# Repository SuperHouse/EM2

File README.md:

EtherMega2
==========
Copyright 2011-2018 Freetronics Pty Ltd www.freetronics.com.au  

The EtherMega2 is an Arduino-compatible board based on the existing
Arduino Mega2560, but with improvements and updates for features and
ease of use. It also includes on-board Ethernet with PoE (Power-over-
Ethernet) support.

Features:

 * High-efficiency switchmode power supply (input voltage 7-28Vdc)
 * Micro-USB Connector
 * microSD card slot
 * 10/100 Ethernet using the Wiznet W5500 chip
 * Overlay guide where you need it (both top and bottom)
 * D13 pin works for everything

You can learn more at:

  https://www.superhouse.tv/em2

INSTALLATION
------------
The design is saved as an EAGLE project. EAGLE PCB design software is
available from www.cadsoftusa.com free for non-commercial use. To use
this project download it and place the directory containing these files
into the "eagle" directory on your computer. Then open EAGLE and
navigate to the project.

DISTRIBUTION
------------
The specific terms of distribution of this project are governed by the
license referenced below.

LICENSE
-------
This work is licensed under the
Creative Commons Attribution-Share Alike License.  
To view a copy of this license, visit

  http://creativecommons.org/licenses/by-sa/3.0/  
  http://creativecommons.org/licenses/by-sa/3.0/legalcode

or send a letter to

  Creative Commons  
  171 Second Street, Suite 300  
  San Francisco  
  California, 94105  
  USA

The "license" folder within this repository also contains copies of the
licences referenced above.

CREDITS
-------
The EtherMega was designed by Jonathan Oxer (jon@freetronics.com) and
Marc Alexander (marc@freetronics.com) based on previous work by the Arduino
team (www.arduino.cc/playground/Main/People) which includes:

 * Massimo Banzi
 * David Cuartielles
 * Tom Igoe
 * Gianluca Martino
 * David A. Mellis

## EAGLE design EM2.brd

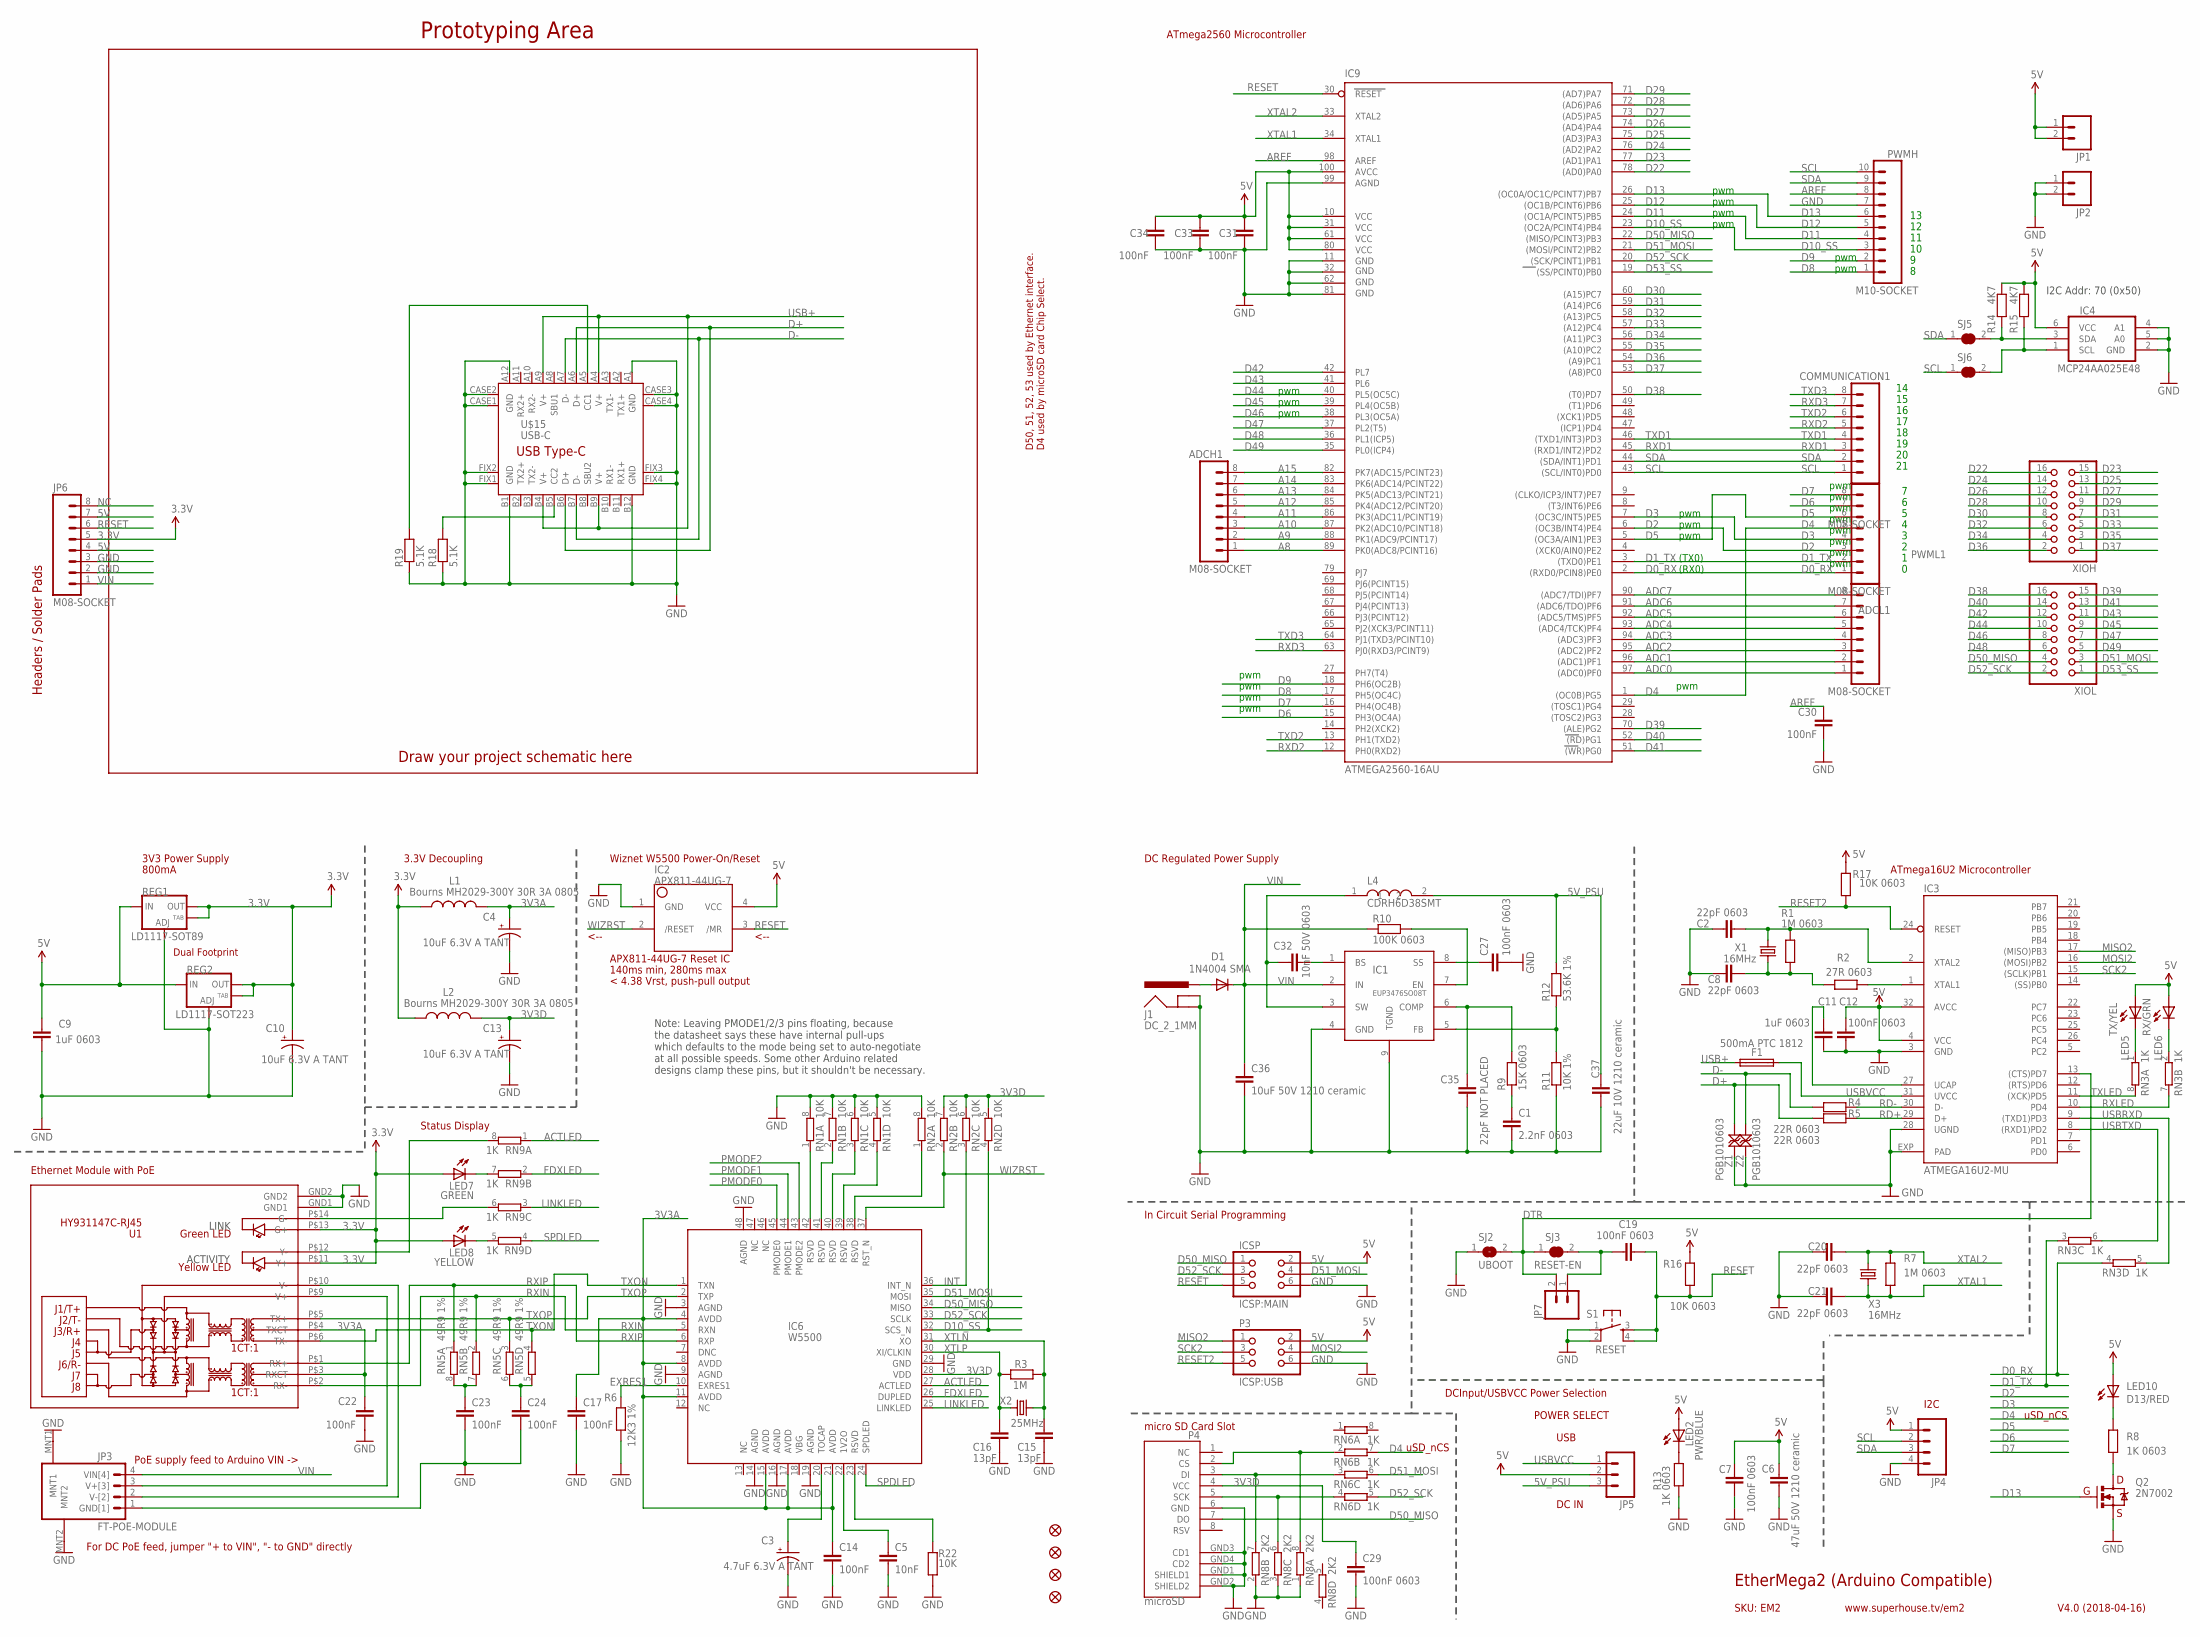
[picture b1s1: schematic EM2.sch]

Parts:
ADCH1: M08-SOCKET; 1X08-S
ADCL1: M08-SOCKET; 1X08-S
C1: 2.2nF 0603; C0603
C2, C8, C20, C21: 22pF 0603; C0603
C3: 4.7uF 6.3V A TANT; EIA3216
C4, C10, C13: 10uF 6.3V A TANT; EIA3216
C5: 10nF; C0603
C6: 47uF 50V 1210 ceramic; C1210
C7, C12, C19, C27, C29: 100nF 0603; C0603
C9, C11: 1uF 0603; C0603
C14, C17, C22, C23, C24, C30, C31, C33, C34: 100nF; C0603
C15, C16: 13pF; C0603
C32: 10nF 50V 0603; C0603
C35: 22pF NOT PLACED; C0603
C36: 10uF 50V 1210 ceramic; C1210
C37: 22uF 10V 1210 ceramic; C1210
COMMUNICATION1: M08-SOCKET; 1X08-S
D1: 1N4004 SMA; SMA-DIODE
F1: 500mA PTC 1812; 1812
FID1, FID2, FID3, FID4: FIDUCIAL1X2.5; FIDUCIAL-1X2.5
IC1: EUP3476SO08T; SO08T
IC2: APX811-44UG-7; SOT143-R
IC3: ATMEGA16U2-MU; ATMEL_QFN32
IC4: MCP24AA025E48; SOT23-6
IC6: W5500
IC9: ATMEGA2560-16AU; TQFP100
ICSP: ICSP:MAIN; 2X03-ICSP
J1: DC_2_1MM; POWER_JACK_SLOTS
JP1, JP2, JP7: M02PTH; 1X02
JP3: FT-POE-MODULE; FT-POE-MODULE-CLEAN
JP4: M04PTH; 1X04
JP5: M03-PIN; 1X03-P
JP6: M08-SOCKET; 1X08-S
L1, L2: Bourns MH2029-300Y 30R 3A 0805; L2012C
L4: CDRH6D38SMT; CDRH
LED2: PWR/BLUE; LED-0603
LED5: TX/YEL; LED-0603
LED6: RX/GRN; LED-0603
LED7: GREEN; LED-0603
LED8: YELLOW; LED-0603
LED10: D13/RED; LED-0603
P3: ICSP:USB; 2X03-ICSP
P4: microSD; MOLEX-SD-500901-003
PWMH: M10-SOCKET; 1X10-S
PWML1: M08-SOCKET; 1X08-S
Q2: 2N7002; SOT23-3
R1, R7: 1M 0603; R0603
R2: 27R 0603; R0603
R3: 1M; R0603
R4, R5: 22R 0603; R0603
R6: 12K3 1%; R0603
R8, R13: 1K 0603; R0603
R9: 15K 0603; R0603
R10: 100K 0603; R0603
R11: 10K 1%; R0603
R12: 53.6K 1%; R0603
R14, R15: 4K7; R0603
R16, R17: 10K 0603; R0603
R18, R19: 5.1K; R0603
R22: 10K; R0603
REG1: LD1117-SOT89; SOT89
REG2: LD1117-SOT223; SOT223
RN1, RN2: 10K; CAY16
RN3, RN6, RN9: 1K; CAY16
RN5: 49R9 1%; CAY16
RN8: 2K2; CAY16
S1: RESET; TACTILE_SMT-6MM
SJ2: UBOOT; SJ
SJ3: RESET-EN; SJC
SJ5, SJ6: SJCN; SJC
U1: HY931147C-RJ45; HY931147C
U$15: USB-C; USB-C-U52A
X1, X3: 16MHz; HC49U-V
X2: 25MHz; HC49U-V
XIOH: PINHD-2X8; 2X08
XIOL: PINHD-2X8; 2X08
Z1, Z2: PGB1010603; TVS0603

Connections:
3.3V: C10.A (+), JP6.5, L1.1, L2.1, LED7.A, LED8.A, REG1.2 (OUT), REG1.4 (OUT), REG2.2 (OUT), REG2.4 (OUT), U1.P$11 (Y+), U1.P$13 (G+)
3V3A: C4.A (+), C14.1, C17.1, C22.1, IC6.4 (AVDD), IC6.8 (AVDD), IC6.11 (AVDD), IC6.15 (AVDD), IC6.17 (AVDD), IC6.21 (AVDD), L1.2, U1.P$3 (RXCT), U1.P$4 (TXCT)
3V3D: C13.A (+), C29.1, IC6.28 (VDD), L2.2, P4.4 (VCC), RN2.5 (2), RN2.6 (2), RN2.7 (2)
5V: C6.2, C7.1, C9.1, C12.1, C31.1, C33.1, C34.1, IC2.4 (VCC), IC3.4 (VCC), IC3.32 (AVCC), IC4.6 (VCC), IC9.10 (VCC), IC9.31 (VCC1), IC9.61 (VCC2), IC9.80 (VCC3), IC9.100 (AVCC), ICSP.2, JP1.1, JP1.2, JP4.1, JP5.2, JP6.4, JP6.7, LED2.A, LED5.A, LED6.A, LED10.A, P3.2, R14.1, R15.1, R16.2, R17.2, REG1.3 (IN), REG2.3 (IN)
5V_PSU: C37.1, JP5.3, L4.2, R12.2
A8: ADCH1.1, IC9.89 (PK0(ADC8/PCINT16))
A9: ADCH1.2, IC9.88 (PK1(ADC9/PCINT17))
A10: ADCH1.3, IC9.87 (PK2(ADC10/PCINT18))
A11: ADCH1.4, IC9.86 (PK3(ADC11/PCINT19))
A12: ADCH1.5, IC9.85 (PK4(ADC12/PCINT20))
A13: ADCH1.6, IC9.84 (PK5(ADC13/PCINT21))
A14: ADCH1.7, IC9.83 (PK6(ADC14/PCINT22))
A15: ADCH1.8, IC9.82 (PK7(ADC15/PCINT23))
ACTLED: IC6.27 (ACTLED), RN9.1
ADC0: ADCL1.1, IC9.97 ((ADC0)PF0)
ADC1: ADCL1.2, IC9.96 ((ADC1)PF1)
ADC2: ADCL1.3, IC9.95 ((ADC2)PF2)
ADC3: ADCL1.4, IC9.94 ((ADC3)PF3)
ADC4: ADCL1.5, IC9.93 ((ADC4/TCK)PF4)
ADC5: ADCL1.6, IC9.92 ((ADC5/TMS)PF5)
ADC6: ADCL1.7, IC9.91 ((ADC6/TDO)PF6)
ADC7: ADCL1.8, IC9.90 ((ADC7/TDI)PF7)
AREF: C30.1, IC9.98 (AREF), PWMH.8
D0_RX: IC9.2 ((RXD0/PCIN8)PE0), PWML1.1, RN3.4 (1)
D1_TX: IC9.3 ((TXD0)PE1), PWML1.2, RN3.3 (1)
D2: IC9.6 ((OC3B/INT4)PE4), PWML1.3
D3: IC9.7 ((OC3C/INT5)PE5), PWML1.4
D4: IC9.1 ((OC0B)PG5), PWML1.5, RN6.7 (2)
D5: IC9.5 ((OC3A/AIN1)PE3), PWML1.6
D6: IC9.15 (PH3(OC4A)), PWML1.7
D7: IC9.16 (PH4(OC4B)), PWML1.8
D8: IC9.17 (PH5(OC4C)), PWMH.1
D9: IC9.18 (PH6(OC2B)), PWMH.2
D10_SS: IC6.32 (SCS_N), IC9.23 ((OC2A/PCINT4)PB4), PWMH.3, RN2.4 (1)
D11: IC9.24 ((OC1A/PCINT5)PB5), PWMH.4
D12: IC9.25 ((OC1B/PCINT6)PB6), PWMH.5
D13: IC9.26 ((OC0A/OC1C/PCINT7)PB7), PWMH.6, Q2.1 (G)
D22: IC9.78 ((AD0)PA0), XIOH.16
D23: IC9.77 ((AD1)PA1), XIOH.15
D24: IC9.76 ((AD2)PA2), XIOH.14
D25: IC9.75 ((AD3)PA3), XIOH.13
D26: IC9.74 ((AD4)PA4), XIOH.12
D27: IC9.73 ((AD5)PA5), XIOH.11
D28: IC9.72 ((AD6)PA6), XIOH.10
D29: IC9.71 ((AD7)PA7), XIOH.9
D30: IC9.60 ((A15)PC7), XIOH.8
D31: IC9.59 ((A14)PC6), XIOH.7
D32: IC9.58 ((A13)PC5), XIOH.6
D33: IC9.57 ((A12)PC4), XIOH.5
D34: IC9.56 ((A11)PC3), XIOH.4
D35: IC9.55 ((A10)PC2), XIOH.3
D36: IC9.54 ((A9)PC1), XIOH.2
D37: IC9.53 ((A8)PC0), XIOH.1
D38: IC9.50 ((T0)PD7), XIOL.16
D39: IC9.70 ((ALE)PG2), XIOL.15
D40: IC9.52 ((RD)PG1), XIOL.14
D41: IC9.51 ((WR)PG0), XIOL.13
D42: IC9.42 (PL7), XIOL.12
D43: IC9.41 (PL6), XIOL.11
D44: IC9.40 (PL5(OC5C)), XIOL.10
D45: IC9.39 (PL4(OC5B)), XIOL.9
D46: IC9.38 (PL3(OC5A)), XIOL.8
D47: IC9.37 (PL2(T5)), XIOL.7
D48: IC9.36 (PL1(ICP5)), XIOL.6
D49: IC9.35 (PL0(ICP4)), XIOL.5
D50_MISO: IC6.34 (MISO), IC9.22 ((MISO/PCINT3)PB3), ICSP.1, P4.7 (DO), XIOL.4
D51_MOSI: IC6.35 (MOSI), IC9.21 ((MOSI/PCINT2)PB2), ICSP.4, RN6.6 (2), XIOL.3
D52_SCK: IC6.33 (SCLK), IC9.20 ((SCK/PCINT1)PB1), ICSP.3, RN6.5 (2), XIOL.2
D53_SS: IC9.19 ((SS/PCINT0)PB0), XIOL.1
D+: R5.2, U$15.A6 (D+), U$15.B6 (D+), Z1.1
D-: R4.2, U$15.A7 (D-), U$15.B7 (D-), Z2.1
DTR: IC3.13 ((CTS)PD7), JP7.2, SJ2.2, SJ3.1
EXRES1: IC6.10 (EXRES1), R6.2
FDXLED: IC6.26 (DUPLED), RN9.2 (1)
GND: C1.2, C2.1, C3.C (-), C4.C (-), C5.2, C6.1, C7.2, C8.1, C9.2, C10.C (-), C11.2, C12.2, C13.C (-), C14.2, C15.2, C16.2, C17.2, C20.1, C21.1, C22.2, C23.2, C24.2, C27.2, C29.2, C30.2, C31.2, C33.2, C34.2, C35.2, C36.2, C37.2, IC1.4 (GND), IC1.9 (TGND), IC2.1 (GND), IC3.3 (GND), IC3.28 (UGND), IC3.EXP (PAD), IC4.2 (GND), IC4.4 (A1), IC4.5 (A0), IC6.3 (AGND), IC6.9 (AGND), IC6.14 (AGND), IC6.16 (AGND), IC6.19 (AGND), IC6.29 (GND), IC6.48 (AGND), IC9.11 (GND), IC9.32 (GND1), IC9.62 (GND2), IC9.81 (GND3), IC9.99 (AGND), ICSP.6, J1.GND, J1.GNDBREAK, JP2.1, JP2.2, JP3.1 (GND[1]), JP3.MNT1, JP3.MNT2, JP4.4, JP6.2, JP6.3, P3.6, P4.6 (GND), P4.GND1 (SHIELD1), P4.GND2 (SHIELD2), P4.GND3 (CD1), P4.GND4 (CD2), PWMH.7, Q2.2 (S), R6.1, R11.1, R13.1, R18.1, R19.1, R22.1, REG1.1 (ADJ), REG2.1 (ADJ), RN1.5 (2), RN1.6 (2), RN1.7 (2), RN1.8 (2), RN2.8 (2), RN8.1, RN8.2 (1), RN8.3 (1), S1.1, S1.2, SJ2.1, U1.GND1, U1.GND2, U$15.A1 (GND), U$15.A12 (GND), U$15.B1 (GND), U$15.B12 (GND), U$15.CASE1 (GND), U$15.CASE2 (GND), U$15.CASE3 (GND), U$15.CASE4 (GND), U$15.FIX1 (GND), U$15.FIX2 (GND), U$15.FIX3 (GND), U$15.FIX4 (GND), Z1.2, Z2.2
INT: IC6.36 (INT_N), RN2.3 (1)
LINKLED: IC6.25 (LINKLED), RN9.3 (1)
MISO2: IC3.17 ((MISO)PB3), P3.1
MOSI2: IC3.16 ((MOSI)PB2), P3.4
unnamed: C24.1, RN5.5 (2), RN5.6 (2)
unnamed: LED10.C, R8.2
unnamed: Q2.3 (D), R8.1
unnamed: IC3.1 (XTAL1), R2.1
unnamed: IC4.1 (SCL), R15.2, SJ6.2
unnamed: LED6.C, RN3.2 (1)
unnamed: LED2.C, R13.2
unnamed: LED5.C, RN3.1
unnamed: R18.2, U$15.B5 (CC2)
unnamed: IC4.3 (SDA), R14.2, SJ5.2
unnamed: P4.5 (SCK), RN6.4 (1), RN8.6 (2)
unnamed: P4.2 (CS), RN6.2 (1), RN8.8 (2)
unnamed: P4.3 (DI), RN6.3 (1), RN8.7 (2)
unnamed: LED8.C, RN9.5 (2)
unnamed: RN9.6 (2), U1.P$14 (G-)
unnamed: D1.A, J1.PWR
unnamed: IC6.39 (RSVD), RN1.4 (1)
unnamed: IC6.40 (RSVD), RN1.3 (1)
unnamed: C27.1, IC1.8 (SS)
unnamed: C1.1, R9.1
unnamed: C35.1, IC1.6 (COMP), R9.2
unnamed: R19.2, U$15.A5 (CC1)
unnamed: JP3.3 (V+[3]), U1.P$9 (V+)
unnamed: JP3.2 (V-[2]), U1.P$10 (V-)
unnamed: C32.1, IC1.3 (SW), L4.1
unnamed: C32.2, IC1.1 (BS)
unnamed: IC1.7 (EN), R10.2
unnamed: IC6.41 (RSVD), RN1.2 (1)
unnamed: C19.1, JP7.1, SJ3.2
unnamed: IC6.42 (RSVD), RN1.1
unnamed: IC1.5 (FB), R11.2, R12.1
unnamed: IC6.23 (RSVD), R22.2
unnamed: IC6.38 (RSVD), RN2.1
unnamed: C5.1, IC6.22 (1V2O)
unnamed: C3.A (+), IC6.20 (TOCAP)
unnamed: C2.2, IC3.2 (XTAL2), R1.2, X1.2
unnamed: C8.2, R1.1, R2.2, X1.1
unnamed: C11.1, IC3.27 (UCAP)
unnamed: C23.1, RN5.7 (2), RN5.8 (2)
unnamed: LED7.C, RN9.7 (2)
unnamed: RN9.8 (2), U1.P$12 (Y-)
NC: JP6.8
PMODE0: IC6.45 (PMODE0)
PMODE1: IC6.44 (PMODE1)
PMODE2: IC6.43 (PMODE2)
RD+: IC3.29 (D+), R5.1
RD-: IC3.30 (D-), R4.1
RESET: C19.2, IC2.3 (/MR), IC9.30 (RESET), ICSP.5, JP6.6, R16.1, S1.3, S1.4
RESET2: IC3.24 (RESET), P3.5, R17.1
RXD1: COMMUNICATION1.3, IC9.45 ((RXD1/INT2)PD2)
RXD2: COMMUNICATION1.5, IC9.12 (PH0(RXD2))
RXD3: COMMUNICATION1.7, IC9.63 (PJ0(RXD3/PCINT9))
RXIN: IC6.5 (RXN), RN5.2 (1), U1.P$2 (RX-)
RXIP: IC6.6 (RXP), RN5.1, U1.P$1 (RX+)
RXLED: IC3.10 (PD4), RN3.7 (2)
SCK2: IC3.15 ((SCLK)PB1), P3.3
SCL: COMMUNICATION1.1, IC9.43 ((SCL/INT0)PD0), JP4.2, PWMH.10, SJ6.1
SDA: COMMUNICATION1.2, IC9.44 ((SDA/INT1)PD1), JP4.3, PWMH.9, SJ5.1
SPDLED: IC6.24 (SPDLED), RN9.4 (1)
TXD1: COMMUNICATION1.4, IC9.46 ((TXD1/INT3)PD3)
TXD2: COMMUNICATION1.6, IC9.13 (PH1(TXD2))
TXD3: COMMUNICATION1.8, IC9.64 (PJ1(TXD3/PCINT10))
TXLED: IC3.11 ((XCK)PD5), RN3.8 (2)
TXON: IC6.1 (TXN), RN5.4 (1), U1.P$6 (TX-)
TXOP: IC6.2 (TXP), RN5.3 (1), U1.P$5 (TX+)
USB+: F1.1, U$15.A4 (V+), U$15.A9 (V+), U$15.B4 (V+), U$15.B9 (V+)
USBRXD: IC3.9 ((TXD1)PD3), RN3.5 (2)
USBTXD: IC3.8 ((RXD1)PD2), RN3.6 (2)
USBVCC: F1.2, IC3.31 (UVCC), JP5.1
VIN: C36.1, D1.C, IC1.2 (IN), JP3.4 (VIN[4]), JP6.1, R10.1
WIZRST: IC2.2 (/RESET), IC6.37 (RST_N), RN2.2 (1)
XTAL1: C21.2, IC9.34 (XTAL1), R7.1, X3.1
XTAL2: C20.2, IC9.33 (XTAL2), R7.2, X3.2
XTLN: C15.1, IC6.31 (XO), R3.1, X2.1
XTLP: C16.1, IC6.30 (XI/CLKIN), R3.2, X2.2

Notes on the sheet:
Prototyping Area
3V3 Power Supply
Status Display
Headers / Solder Pads
Dual Footprint
3.3V Decoupling
Draw your project schematic here
D50, 51, 52, 53 used by Ethernet interface.
PoE supply feed to Arduino VIN ->
For DC PoE feed, jumper "+ to VIN", "- to GND" directly
DC Regulated Power Supply
ATmega2560 Microcontroller
APX811-44UG-7 Reset IC
140ms min, 280ms max
ATmega16U2 Microcontroller
DCInput/USBVCC Power Selection
Wiznet W5500 Power-On/Reset
uSD_nCS
800mA
In Circuit Serial Programming
micro SD Card Slot
EtherMega2 (Arduino Compatible)
V4.0 (2018-04-16)
www.superhouse.tv/em2
SKU: EM2
Ethernet Module with PoE
< 4.38 Vrst, push-pull output
<--
D4 used by microSD card Chip Select.
pwm
(TX0)
(RX0)
I2C
USB
DC IN
POWER SELECT
I2C Addr: 70 (0x50)
LINK
ACTIVITY
Note: Leaving PMODE1/2/3 pins floating, because the datasheet says these have internal pull-ups which defaults to the mode being set to auto-negotiate at all possible speeds. Some other Arduino related designs clamp these pins, but it shouldn't be necessary.

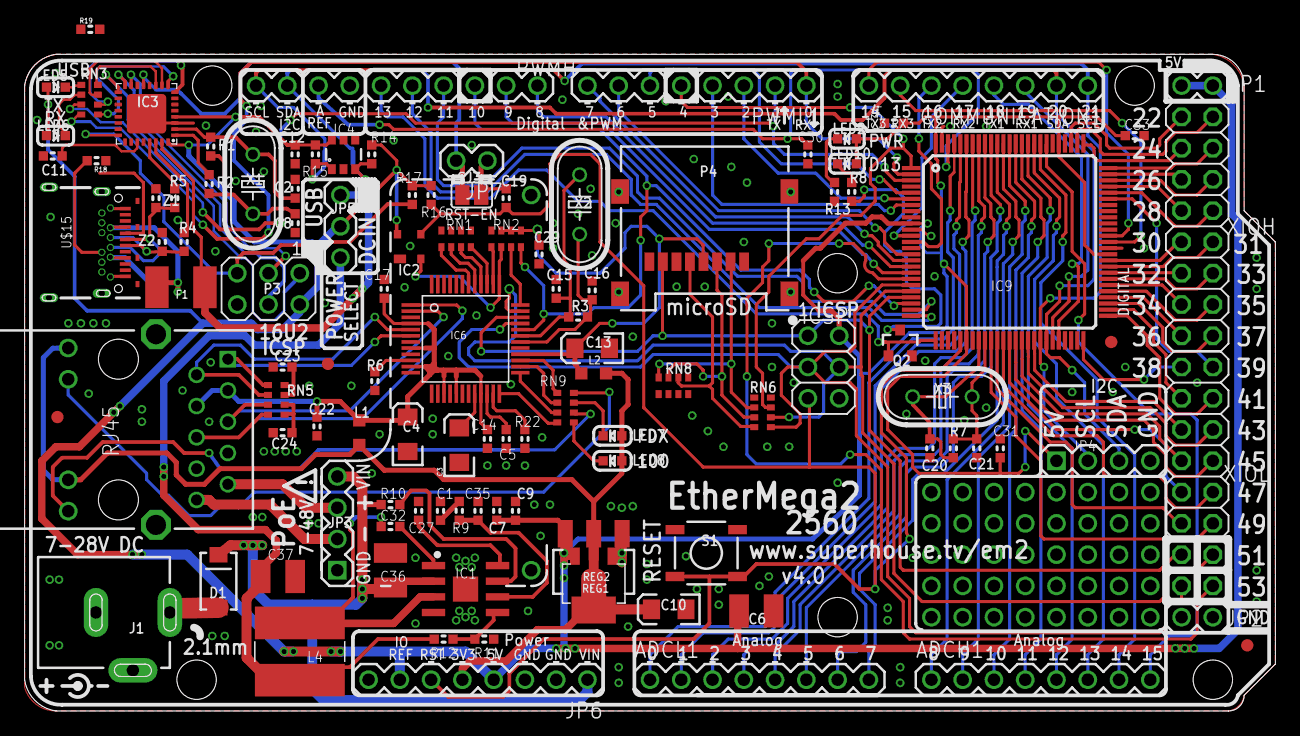
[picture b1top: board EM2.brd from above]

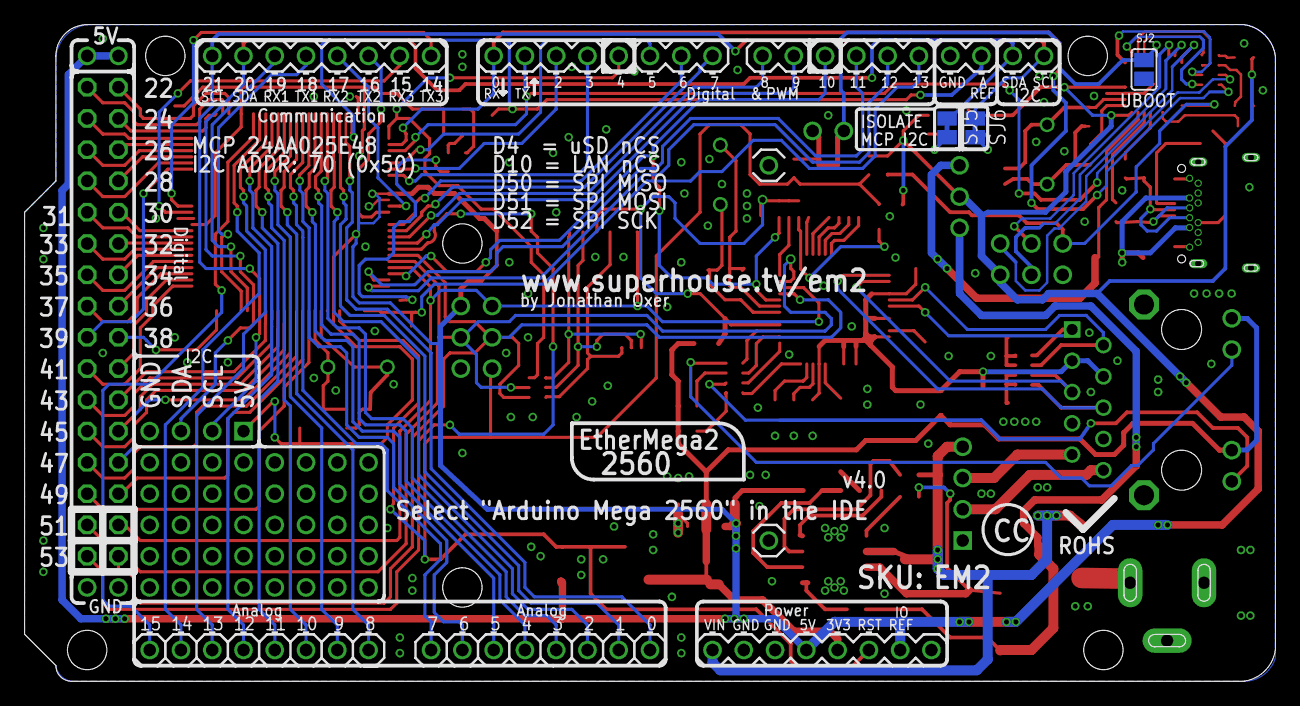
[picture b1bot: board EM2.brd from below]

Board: 2 copper layers, 101.6 x 53.3 mm, 114 parts (3 on the bottom side), 150 nets.

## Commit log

2018-04-11 Renamed project for major update to W5500
2018-04-16 Major rework using W5500 ethernet chip
2018-05-16 Finished conversion to W5500 and all DRC for release
2019-04-23 Changed USB socket
2019-11-19 Library part migration to SuperHouse
